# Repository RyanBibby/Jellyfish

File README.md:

EMF Jellyfish

- 3D Print files
- Firmware
- Depricated firmware
- Hardware designs

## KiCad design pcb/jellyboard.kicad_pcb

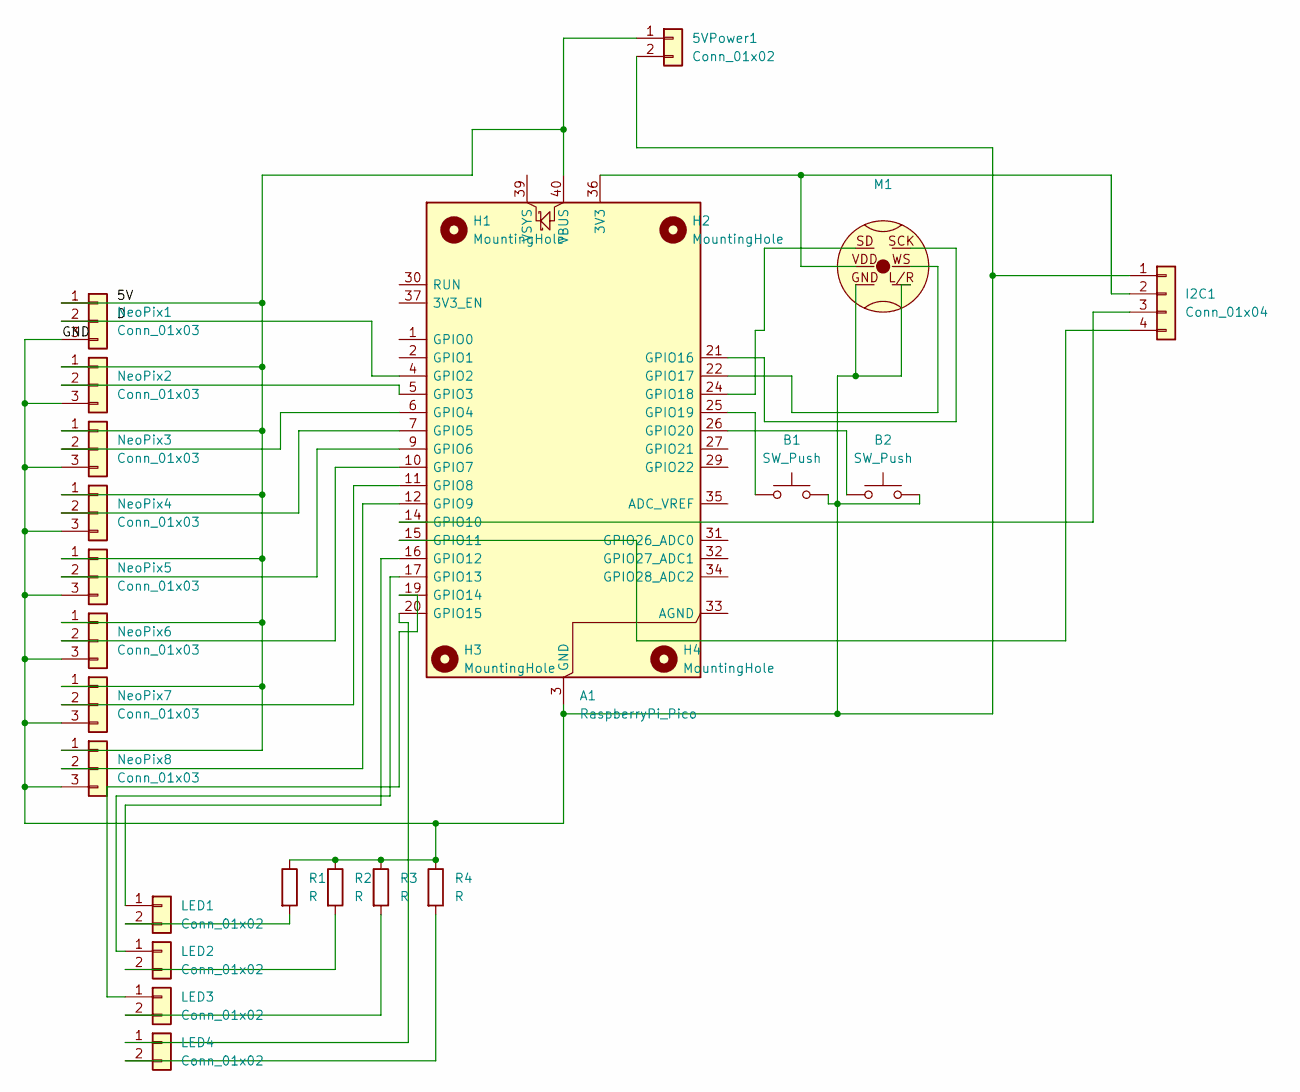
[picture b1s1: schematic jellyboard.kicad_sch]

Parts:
5VPower1: Conn_01x02; SolderJumper-2_P1.3mm_Open_Pad1.0x1.5mm
A1: RaspberryPi_Pico; RaspberryPi_Pico_Common_Unspecified
B1, B2: SW_Push; SW_PUSH_6mm_H4.3mm
H1, H2, H3, H4: MountingHole; MountingHole_2.1mm
I2C1: Conn_01x04; PinHeader_1x04_P2.54mm_Vertical
LED1, LED2, LED3, LED4: Conn_01x02; PinHeader_1x02_P2.54mm_Vertical
M1: inmp441_2x3
NeoPix1, NeoPix2, NeoPix3, NeoPix4, NeoPix5, NeoPix6, NeoPix7, NeoPix8: Conn_01x03; PinHeader_1x03_P2.54mm_Vertical
R1, R2, R3, R4: R; R_Axial_DIN0204_L3.6mm_D1.6mm_P7.62mm_Horizontal

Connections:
/5V: 5VPower1.1, A1.40 (VBUS), NeoPix1.1, NeoPix2.1, NeoPix3.1, NeoPix4.1, NeoPix5.1, NeoPix6.1, NeoPix7.1, NeoPix8.1; also elsewhere on the board
/D: A1.4 (GPIO2), NeoPix1.2
/GND: 5VPower1.2, A1.3 (GND), A1.8 (GND), A1.13 (GND), A1.18 (GND), A1.23 (GND), A1.28 (GND), A1.38 (GND), B1.2, B2.2, I2C1.1, M1.GND, M1.L/R, NeoPix1.3, NeoPix2.3, NeoPix3.3, NeoPix4.3, NeoPix5.3, NeoPix6.3, NeoPix7.3, NeoPix8.3, R1.1, R2.1, R3.1, R4.1; also elsewhere on the board
unnamed 3: A1.36 (3V3), I2C1.2, M1.VDD; also elsewhere on the board
unnamed: A1.5 (GPIO3), NeoPix2.2
unnamed: A1.6 (GPIO4), NeoPix3.2
unnamed: A1.7 (GPIO5), NeoPix4.2
unnamed: A1.9 (GPIO6), NeoPix5.2
unnamed: A1.10 (GPIO7), NeoPix6.2
unnamed: A1.11 (GPIO8), NeoPix7.2
unnamed: A1.12 (GPIO9), NeoPix8.2
unnamed 11: A1.14 (GPIO10), I2C1.3; also elsewhere on the board
unnamed 12: A1.15 (GPIO11), I2C1.4; also elsewhere on the board
unnamed: A1.16 (GPIO12), LED1.1
unnamed: A1.17 (GPIO13), LED2.1
unnamed: A1.19 (GPIO14), LED3.1
unnamed: A1.20 (GPIO15), LED4.1
unnamed: A1.21 (GPIO16), M1.SCK
unnamed: A1.22 (GPIO17), M1.WS
unnamed: A1.24 (GPIO18), M1.SD
unnamed: A1.25 (GPIO19), B1.1
unnamed: A1.26 (GPIO20), B2.1
unnamed: LED1.2, R1.2
unnamed: LED2.2, R2.2
unnamed: LED3.2, R3.2
unnamed: LED4.2, R4.2

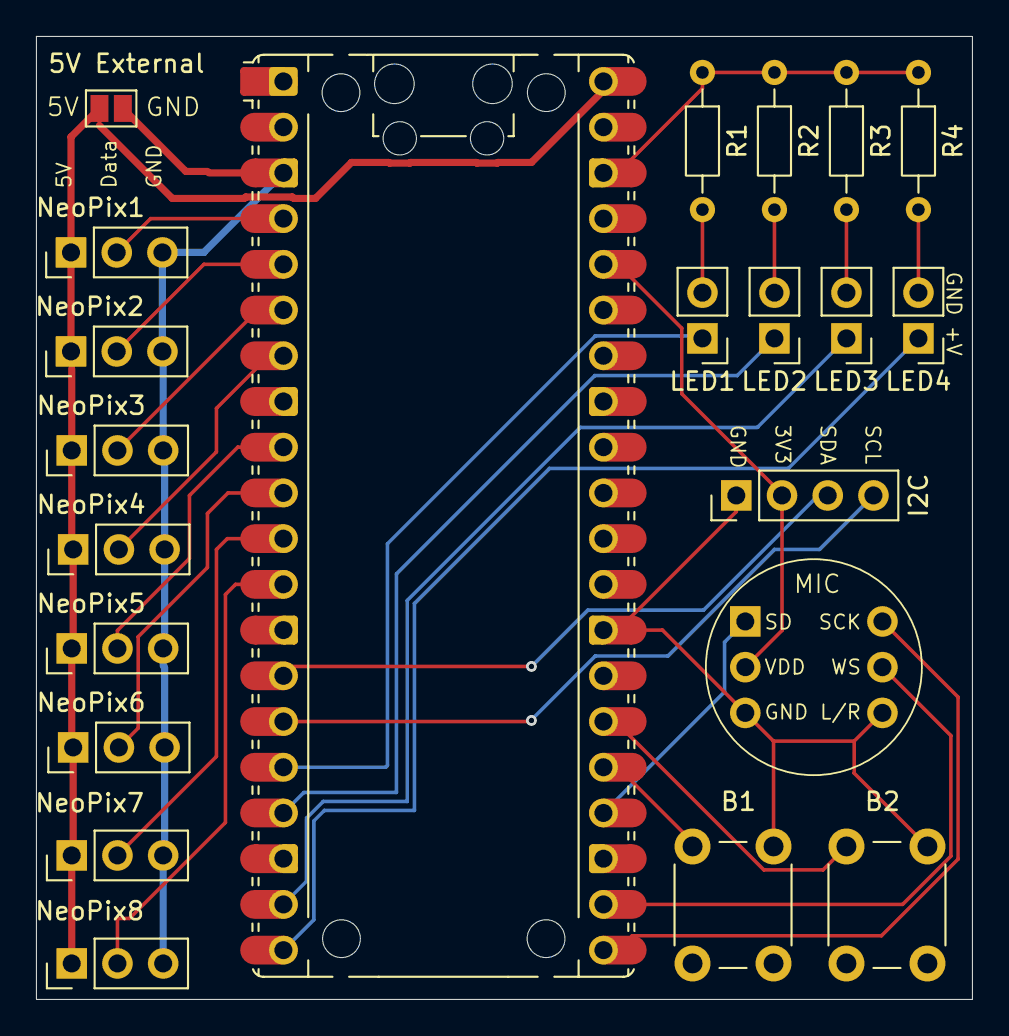
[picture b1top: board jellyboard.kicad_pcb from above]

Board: 2 copper layers, 52.0 x 53.5 mm, 26 parts (0 on the bottom side), 26 nets.

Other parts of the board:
5V External: Conn_01x02; SolderJumper-2_P1.3mm_Open_Pad1.0x1.5mm
I2C: Conn_01x04; PinHeader_1x04_P2.54mm_Vertical

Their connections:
/5V: 5V External.1; also elsewhere on the board
/GND: 5V External.2, I2C.1; also elsewhere on the board
unnamed 3: I2C.2; also elsewhere on the board
unnamed 11: I2C.3; also elsewhere on the board
unnamed 12: I2C.4; also elsewhere on the board

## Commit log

2026-03-25 Added the PCB files and gerbers
2026-03-30 Refactor JellyOS to use AudioVisualizer and simplify code
    Removed old LED setup and animation logic, integrated AudioVisualizer for hardware control, and updated the main loop to use audio volume for color effects.
2026-04-04 Rename JellyOS.py to JellyOS.py
2026-04-04 Rename hardware.py to hardware.py
2026-04-05 Updated build
2026-04-05 Make CLion happy
